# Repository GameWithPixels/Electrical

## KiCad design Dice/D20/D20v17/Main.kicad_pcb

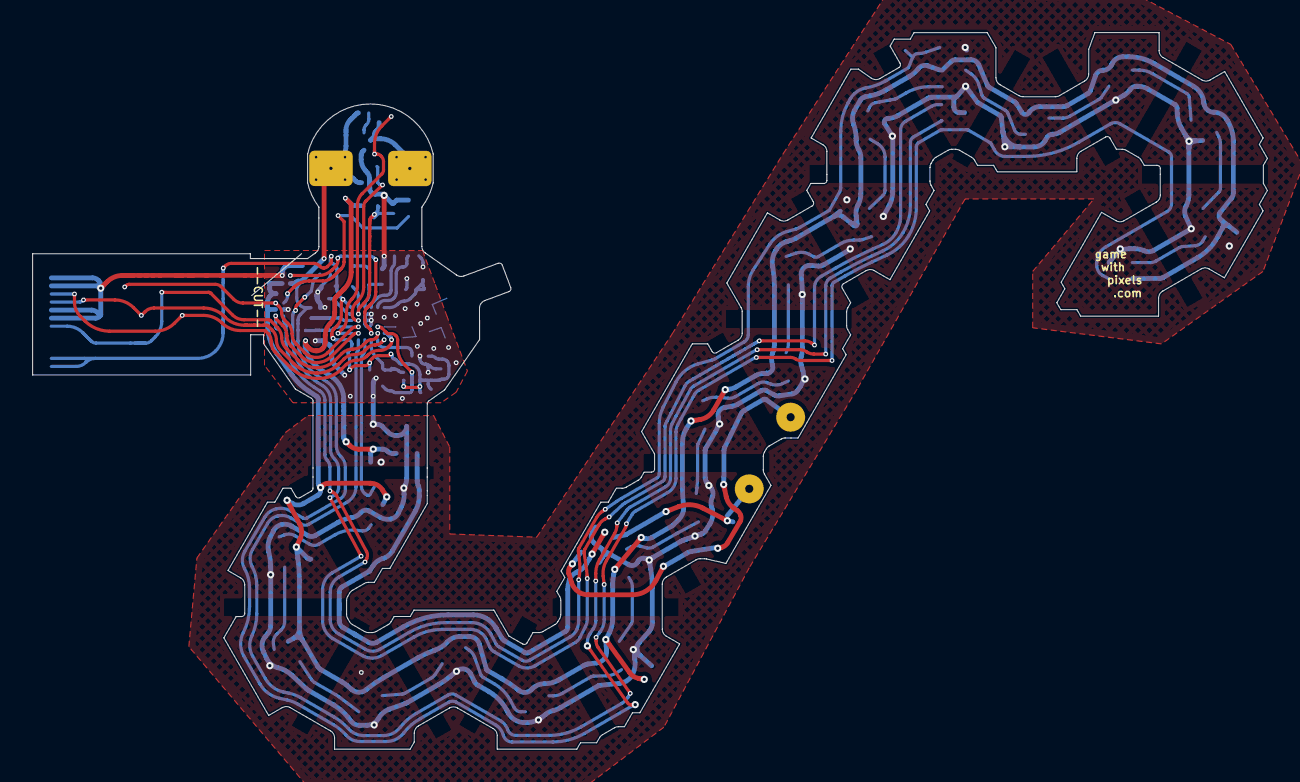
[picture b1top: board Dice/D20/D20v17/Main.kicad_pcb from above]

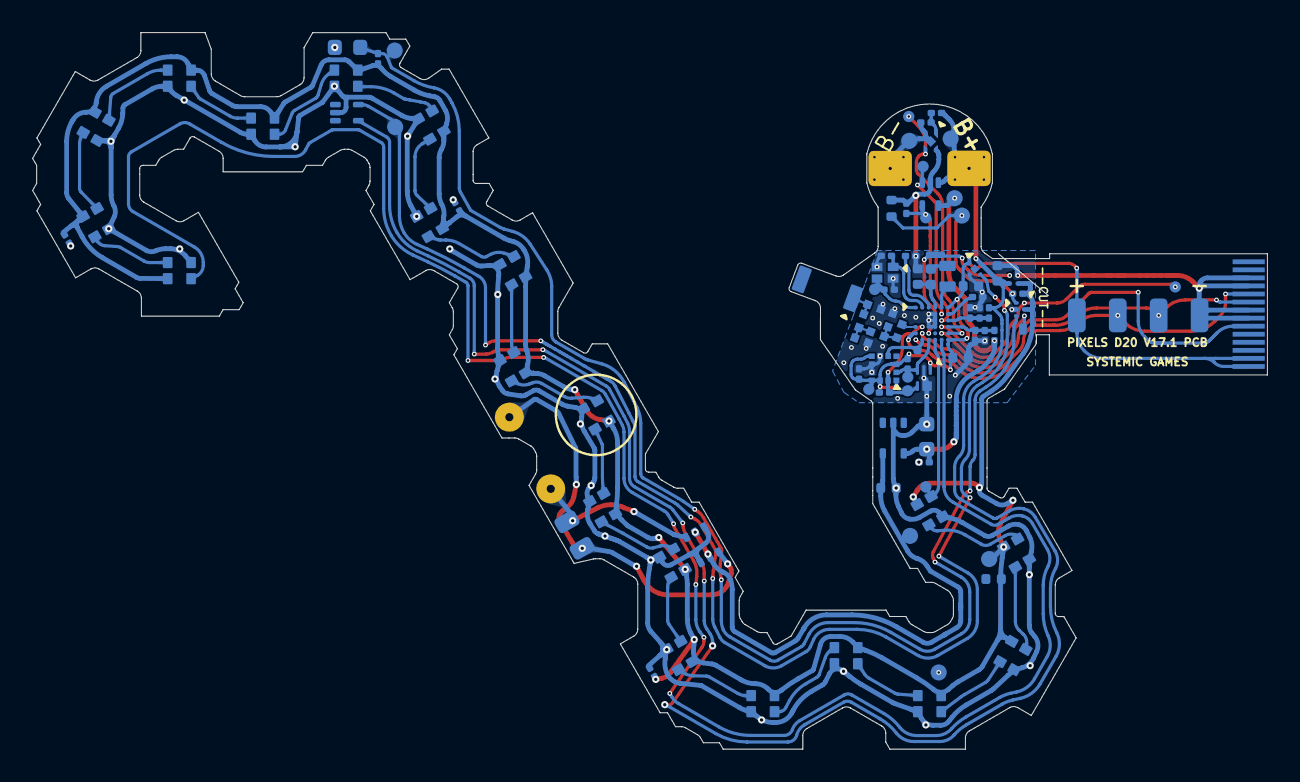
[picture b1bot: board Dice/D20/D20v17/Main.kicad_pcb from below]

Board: 2 copper layers, 76.7 x 44.5 mm, 99 parts (99 on the bottom side), 59 nets.

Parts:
AE1: Antenna_Chip; CHIP_ANT
C1, C4, C18: 4.7uF 10V 20%; C_0402_1005Metric
C2, C5: 8pF 10V 10%; C_0201_0603Metric
C3, C6, C10, C23, C24, C25: 0.1uF 10V 20%; C_0201_0603Metric
C7: 100pF NP0 10V 2%; C_0201_0603Metric
C8: 1.2pF 10V 5% C0G; 0402_RF
C9, C16: 10uF 6.3V 20%; C_0402_1005Metric
C11, C12: DNP; 0402_RF
C13: 4.7uF 25V 20%; C_0402_1005Metric
C15: 22uF 10V 20%; C_0603_1608Metric
C19: 12nF 50V 5% NP0; C_0805_2012Metric
C21, C22: 10nF 25V 10%; C_0201_0603Metric
D1: BAV99S; SOT-363_SC-70-6
D2, D3, D4, D5, D6, D7, D8, D9, D10, D11, D12, D13, D14, D15, D16, D17, D18, D19, D20, D21: TX1812MJA5; TX1812MWCA5-F01
J1: Conn_01x14; FPC_14
J2: Conn_01x04; FPC-POGO-4
J3: Conn_01x02; Hongjie 10100 Solder Tabs
L1: 10uH 100mA 20%; C_1.2x1.8
L2: 15nH 100mA 5%; L_0402_1005Metric
L3: 0 Ohm; 0402_RF
L4: 2.2nH 5%; 0402_RF
L5: 3.3nH 5%; 0402_RF
P5: COILA; TestPoint_THTPad_D1.5mm_Drill0.7mm_nosilk
P6: COILB; TestPoint_THTPad_D1.5mm_Drill0.7mm_nosilk
Q1: ZSPT-Z1608C-06F-Z4; D_0603_1608Metric
R1, R2, R7: 3.9M 1%; R_0201_0603Metric
R4, R5: 10k 1%; R_0201_0603Metric
R6, R10, R11: 3.9k 1%; R_0201_0603Metric
R8: 10M 1%; R_0201_0603Metric
R9: 100k 1%; R_0201_0603Metric
R12: 510R 1%; R_0201_0603Metric
TH1: NTC 100k @ 25C; R_0402_1005Metric
U1: NRF52810-CAAA-R; WLCSP
U2: KXTJ3-1057; LGA-12_2x2mm_P0.5mm
U3: TPS715; SOT-353_SC-70-5
U4: M24C02-FMH6TG; UFDFPN5
U5: AW35122
U6: ME6230; FPB1_1-4
U7: DS6101; UDFN-4-1EP_1x1mm_P0.65mm_EP0.48x0.48mm
U8: SL1605; SOT-553
U9: XT4051; SOT-553
U10: WAS3157D-6/TR; DFN1109-6
W1: LED_DATA1; TEST_PIN
W2: PROG; TEST_PIN
W3: PHOTO; TEST_PIN
W4: VDC; TEST_PIN
W5: SM; TEST_PIN
W6: MAG1; TEST_PIN
W7: ACC; TEST_PIN
W8: SCL; TEST_PIN
W9: SDA; TEST_PIN
W11: XC1; TEST_PIN
W14: BATT; TEST_PIN
W15: +5V; TEST_PIN
W16: VIN; TEST_PIN
W17: STAT; TEST_PIN
W19: GND; TEST_PIN
W20: TH1; TEST_PIN
W21: LED2; TEST_PIN
W22: ADC_S; TEST_PIN
W23: ADC_OUT; TEST_PIN
W24: B-; TEST_PIN
W25: VDD; TEST_PIN
Y1: 32MHz 40ppm; SX16Y032000B81T001

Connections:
+5V: C15.1, R1.1, R4.1, U3.5 (VOUT), U9.5 (VCC), W15.1
+BATT: C16.1, J3.1, R7.1, R12.1, U5.A2 (VIN), U6.4 (VIN), U8.4 (VDD), U9.1 (BAT), W14.1
/5V_SENSE: C21.1, R1.2, R2.2, U1.E6 (P0.05/AIN3)
/ACC_INT: U1.G2 (P0.20/TCLK), U2.5 (INT), W7.1
/ANTENNA: AE1.1 (FEED), C11.1, L3.2
/ANT_50: C12.1, L3.1, L5.2
/ANT_MID: C8.1, L4.2, L5.1
/ANT_NRF: L4.1, U1.E1 (ANT)
/LED_DATA: D2.3 (DIN), U1.G4 (P0.15), W1.1
/LED_EN: U1.F3 (P0.17), U5.B2 (EN), W21.1
/LED_RETURN: D21.1 (DOUT), U1.G5 (P0.12)
/MAG1_: U6.3 (CE), U8.5 (OUT), W6.1
/NTC_PHOTO_SENSE: U1.E5 (P0.04/AIN2), U10.6 (A), W23.1
/OPT_A2D: Q1.1 (C), R5.2, U10.3 (B1), W3.1
/PROG: R6.1, U1.B5 (P0.00/XL1), U9.4 (PROG), W2.1
/SCL: R10.2, U1.E2 (P0.18/TDATA0), U2.12 (SCL), U4.4 (SCL), W8.1
/SDA: R11.2, U1.G3 (P0.16/TDATA1), U2.2 (SDA), U4.3 (SDA), W9.1
/SENSE_SELECT: U1.F5 (P0.11), U10.4 (S), W22.1
/SM: U1.F6 (P0.8), U7.3 (SM), W5.1
/STATS: U1.D5 (P0.01/XL2), U9.3 (CHRG), W17.1
/VBAT_SENSE: C22.1, R7.2, R8.1, U1.D6 (P0.03/AIN1)
/Wireless Charging/B-: C23.2, J3.2, U7.2 (VSS), U7.5 (PAD), W24.1
/Wireless Charging/COILA: C19.1, D1.3 (K1A2), P5.1
/Wireless Charging/COILB: C19.2, D1.6 (K3A4), P6.1
/Wireless Charging/TH1: R9.2, TH1.1, U10.1 (B0), W20.1
GND: C1.2, C2.1, C3.2, C4.2, C5.1, C6.2, C7.2, C8.2, C9.2, C10.2, C11.2, C12.2, C13.2, C15.2, C16.2, C18.2, C21.2, C22.2, C24.2, C25.2, D1.1 (A1), D1.4 (A3), D2.2 (GND), D3.2 (GND), D4.2 (GND), D5.2 (GND), D6.2 (GND), D7.2 (GND), D8.2 (GND), D9.2 (GND), D10.2 (GND), D11.2 (GND), D12.2 (GND), D13.2 (GND), D14.2 (GND), D15.2 (GND), D16.2 (GND), D17.2 (GND), D18.2 (GND), D19.2 (GND), D20.2 (GND), D21.2 (GND), J1.3, J1.4, J1.7, J1.8, J2.4, Q1.2 (E), R2.1, R4.2, R6.2, R8.2, TH1.2, U1.B3 (VSS), U1.B4 (VSS), U1.C1 (VSS_PA), U1.D3 (VSS), U1.D4 (VSS), U1.E3 (VSS), U1.E4 (VSS), U2.6 (GND), U2.8 (GND), U2.9 (GND), U3.2 (GND), U4.2 (VSS), U4.5 (WP), U5.B1 (GND), U6.2 (VSS), U7.4 (EB-), U8.2 (GND), U9.2 (GND), U10.2 (GND), W19.1, Y1.2, Y1.4
unnamed: D2.1 (DOUT), D3.3 (DIN)
unnamed: D3.1 (DOUT), D4.3 (DIN)
unnamed: D4.1 (DOUT), D5.3 (DIN)
unnamed: D5.1 (DOUT), D6.3 (DIN)
unnamed: D6.1 (DOUT), D7.3 (DIN)
unnamed: D7.1 (DOUT), D8.3 (DIN)
unnamed: D8.1 (DOUT), D9.3 (DIN)
unnamed: D9.1 (DOUT), D10.3 (DIN)
unnamed: D10.1 (DOUT), D11.3 (DIN)
unnamed: D11.1 (DOUT), D12.3 (DIN)
unnamed: D12.1 (DOUT), D13.3 (DIN)
unnamed: D13.1 (DOUT), D14.3 (DIN)
unnamed: D14.1 (DOUT), D15.3 (DIN)
unnamed: D15.1 (DOUT), D16.3 (DIN)
unnamed: D16.1 (DOUT), D17.3 (DIN)
unnamed: D17.1 (DOUT), D18.3 (DIN)
unnamed: D18.1 (DOUT), D19.3 (DIN)
unnamed: D19.1 (DOUT), D20.3 (DIN)
unnamed: D20.1 (DOUT), D21.3 (DIN)
unnamed: L1.2, L2.1
unnamed: L1.1, U1.A5 (DCC)
unnamed: C3.1, U1.B6 (DEC1)
unnamed: C7.1, U1.A3 (DEC2)
unnamed: C1.1, L2.2, U1.A4 (DEC4)
unnamed: C5.2, U1.A1 (XC1), W11.1, Y1.3
unnamed: C2.2, U1.A2 (XC2), Y1.1
unnamed: C23.1, R12.2, U7.1 (BAT)
RESET: J1.9, U1.F2 (P0.21)
SWDCLK: J1.6, J2.3, U1.G1 (SWDCLK)
SWDIO: J1.5, J2.2, U1.F1 (SWDIO)
VDC: C6.1, C9.1, C24.1, C25.1, D2.4 (VCC), D3.4 (VCC), D4.4 (VCC), D5.4 (VCC), D6.4 (VCC), D7.4 (VCC), D8.4 (VCC), D9.4 (VCC), D10.4 (VCC), D11.4 (VCC), D12.4 (VCC), D13.4 (VCC), D14.4 (VCC), D15.4 (VCC), D16.4 (VCC), D17.4 (VCC), D18.4 (VCC), D19.4 (VCC), D20.4 (VCC), D21.4 (VCC), R5.1, R9.1, U5.A1 (VOUT), U10.5 (VCC), W4.1
VDD: C4.1, C10.1, C18.1, J1.13, J1.14, J2.1, R10.1, R11.1, U1.A6 (VDD), U1.G6 (VDD), U2.1 (ADDR), U2.3 (IO_VDD), U2.7 (VDD), U2.10 (VDD), U2.11 (IO_VDD), U4.1 (VCC), U6.1 (VOUT), W25.1
VEE: C13.1, D1.2 (K2), D1.5 (K4), U3.4 (VIN), W16.1

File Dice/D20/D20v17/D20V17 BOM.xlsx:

Reference | Value | Footprint | Qty | Manufacturer | Part Number | LCSC Part # |  | Alternate Manufacturer | Alternate PN | Alternate LCSC Part #
AE1 | Antenna_Chip | Pixels-dice:CHIP_ANT | 1 | Microgate | MGMA3216H2450-A02 | C486319
C1,C4,C18 | 4.7uF 10V 20% | Pixels-dice:C_0402_1005Metric | 3 | Murata | GRM155R61A475MEAAJ | C1849652 |  | Samsung Electro-Mechanics | CL05A475MP5NRNC | C23733
C2,C5 | 8pF 10V 10% | Capacitor_SMD:C_0201_0603Metric | 2 | FH (Guangdong Fenghua Advanced Tech) | 0201CG8R0C500NT | C501818 |  | Samsung Electro-Mechanics | CL10A475KA8NQNC
C3,C6,C10,C23,C24,C25 | 0.1uF 10V 20% | Capacitor_SMD:C_0201_0603Metric | 6 | HRE | CGA0201X5R104K100ET | C6119757
C7 | 100pF NP0 10V 2% | Capacitor_SMD:C_0201_0603Metric | 1 | HRE | CGA0201C0G101J500ET | C20069263 |  | EYANG(Shenzhen Eyang Tech Development) | C0201C0G101J500NTA | C115540
C8 | 1.2pF 10V 5% C0G | Pixels-dice:0402_RF | 1 | HRE | CGA0402C0G1R2C500GT | C20069293 |  | VIIYONG | V1R2B0402C0G500NBT | C513431
C9,C16 | 10uF 6.3V 20% | Pixels-dice:C_0402_1005Metric | 2 | HRE | CGA0402X5R106M6R3GT | C23692971
C13 | 4.7uF 25V 20% | Capacitor_SMD:C_0402_1005Metric | 1 | HRE | CGA0402X5R475M250GT | C6119795
C15 | 22uF 10V 20% | Capacitor_SMD:C_0603_1608Metric | 1 | HRE | CGA0603X5R226M100JT | C6119863
C19 | 12nF 50V 5% NP0 | Capacitor_SMD:C_0805_2012Metric | 1 | Murata | GRM2195C1H123JA01D | C97906
C21,C22 | 10nF 25V 10% | Capacitor_SMD:C_0201_0603Metric | 2 | HRE | CGA0201X5R103K250ET | C7503521 |  | Murata Electronics | GRM033R71A103KA01D | C76941
D1 | BAV99S | Pixels-dice:SOT-363_SC-70-6 | 1 | Nexperia | BAV99S,115 | C96225
D2,D3,D4,D5,D6,D7,D8,D9,D10,D11,D12,D13,D14,D15,D16,D17,D18,D19,D20,D21 | TX1812MJA5 | Pixels-dice:TX1812MWCA5-F01 | 20 | TCWIN | TX1812MJA5-F01
L1 | 10uH 100mA 20% | Pixels-dice:C_1.2x1.8 | 1 | Sunltech Tech | SLC1608F100KTT | C411908
L2 | 15nH 100mA 5% | Inductor_SMD:L_0402_1005Metric | 1 | FH | VHF100505H15NKT | C381880 |  | SUNLORD | MCL2012H100MT
L3 | 0 Ohm | Pixels-dice:0402_RF | 1 | UNI-ROYAL(Uniroyal Elec) | 0402WGJ0000TCE | C21376
L4 | 2.2nH 5% | Pixels-dice:0402_RF | 1 | FH | VHF100505HQ2N2ST | C395061
L5 | 3.3nH 5% | Pixels-dice:0402_RF | 1 | FH | VHF100505HQ3N3ST | C395065
Q1 | ZSPT-Z1608C-06F-Z4 | Diode_SMD:D_0603_1608Metric | 1 | Chau Light | ZSPT-Z1608C-06F-Z4 | C5337512
R1,R2,R7 | 3.9M 1% | Resistor_SMD:R_0201_0603Metric | 3 | UNI-ROYAL(Uniroyal Elec) | 0201WMF3904TEE | C423545 |  | RALEC | RTT013904FTH | C166210
R4,R5 | 10k 1% | Resistor_SMD:R_0201_0603Metric | 2 | UNI-ROYAL(Uniroyal Elec) | 0201WMF1002TEE | C473048
R6,R10,R11 | 3.9k 1% | Resistor_SMD:R_0201_0603Metric | 3 | UNI-ROYAL(Uniroyal Elec) | 0201WMF3651TEE | C516477 |  | UNI-ROYAL(Uniroyal Elec)
R8 | 10M 1% | Resistor_SMD:R_0201_0603Metric | 1 | UNI-ROYAL(Uniroyal Elec) | 0201WMF1005TEE | C423797
R9 | 100k 1% | Resistor_SMD:R_0201_0603Metric | 1 | UNI-ROYAL(Uniroyal Elec) | 0201WMF1003TEE | C270364
R12 | 510R 1% | Resistor_SMD:R_0201_0603Metric | 1 | UNI-ROYAL(Uniroyal Elec) | NQ01WMJ0511TEE | C965307
TH1 | NTC 100k @ 25C | Pixels-dice:R_0402_1005Metric | 1 | TDK | NTCG104EF104FT1X | C107344
U1 | NRF52810-CAAA-R | Pixels-dice:WLCSP | 1 | Nordic | NRF52810-CAAA-R | C3606661
U2 | KXTJ3-1057 | Package_LGA:LGA-12_2x2mm_P0.5mm | 1 | Kionix | KXTJ3-1057 | C442603
U3 | TPS715 | Package_TO_SOT_SMD:SOT-353_SC-70-5 | 1 | TECH PUBLIC | TPS71550DCKR-TP | C7202975 |  | Texas Instruments | TPS71550DCKR | C571193
U4 | M24C02-FMH6TG | Pixels-dice:UFDFPN5 | 1 | STMicroelectronics | M24C02-FMH6TG | C222197
U5 | AW35122 | Pixels-dice:AW35122 | 1 | AWINIC(Shanghai Awinic Tech) | AW35122FDR | C5125911
U6 | ME6230 | Pixels-dice:FPB1_1-4 | 1 | MICRONE(Nanjing Micro One Elec) | ME6230C30U4AG | C2925772 |  | ChipLink Tech | CL9906A30F4N | C5297658
U7 | DS6101 | Package_DFN_QFN:UDFN-4-1EP_1x1mm_P0.65mm_EP0.48x0.48mm | 1 | DSTECH | DS6101AED4 | C7499469
U8 | SL1605 | Package_TO_SOT_SMD:SOT-553 | 1 | Slkor(SLKORMICRO Elec.) | SL1605TL | C2826474
U9 | XT4051 | Package_TO_SOT_SMD:SOT-553 | 1 | NATLINEAR | XT4051K421KR-G | C219186
U10 | WAS3157D-6/TR | Pixels-dice:DFN1109-6 | 1 | WILLSEMI(Will Semicon) | WAS3157D-6/TR | C2939860
Y1 | 32MHz 40ppm | Pixels-dice:SX16Y032000B81T001 | 1 | TKD | SX16Y032000B81T001 | C20623629 |  | TXC Corp | 8Q32000002 | C5203640

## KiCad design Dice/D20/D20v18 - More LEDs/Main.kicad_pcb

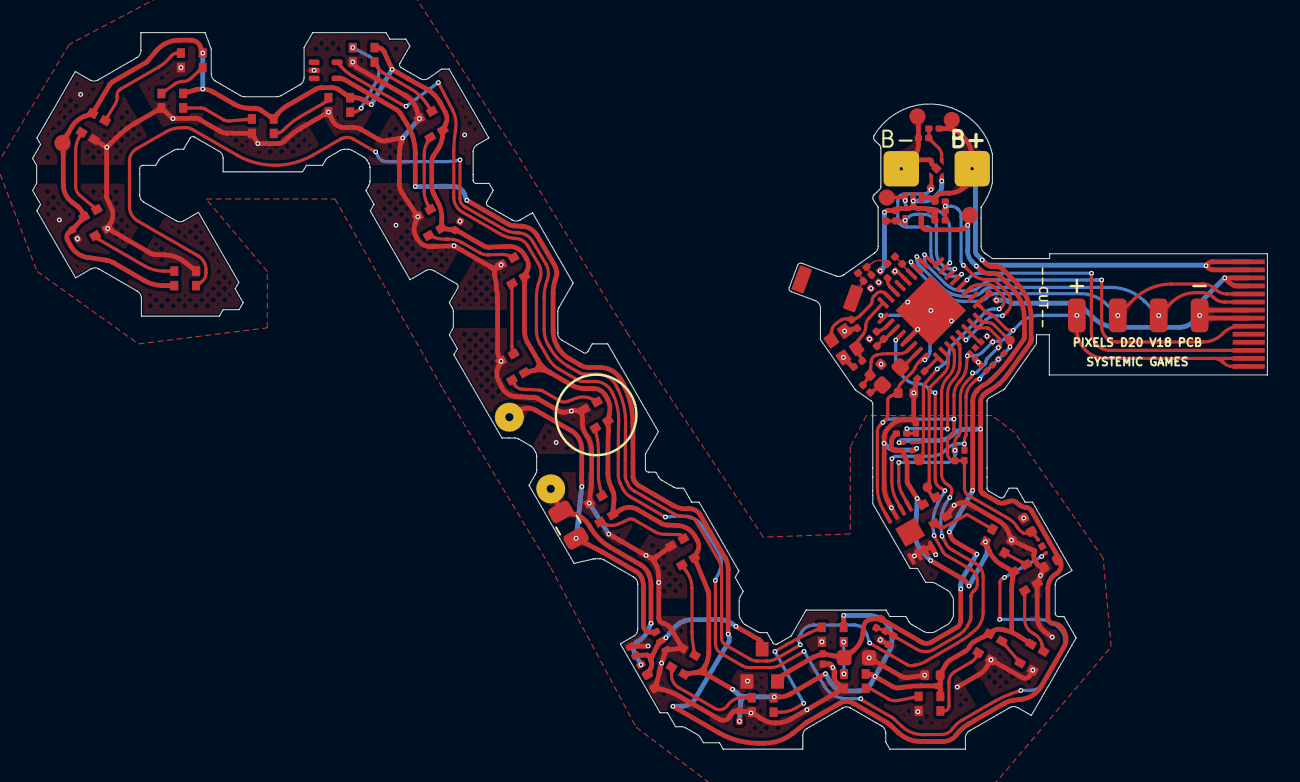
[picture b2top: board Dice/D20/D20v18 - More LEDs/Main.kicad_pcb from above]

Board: 2 copper layers, 76.7 x 44.5 mm, 92 parts (1 on the bottom side), 63 nets.

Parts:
AE1: Antenna_Chip; CHIP_ANT
C1, C4, C18: 4.7uF 10V 20%; C_0402_1005Metric
C2, C5: 8pF 10V 10%; C_0201_0603Metric
C3, C6, C10, C23, C24, C25: 0.1uF 10V 20%; C_0201_0603Metric
C7: 100pF NP0 10V 2%; C_0201_0603Metric
C8: 0.8pF 10V 5% C0G; C_0201_0603Metric
C9, C16: 10uF 6.3V 20%; C_0402_1005Metric
C11, C12: DNP; C_0201_0603Metric
C13: 4.7uF 25V 20%; C_0402_1005Metric
C15: 22uF 10V 20%; C_0603_1608Metric
C19: 12nF 50V 5% NP0; C_0805_2012Metric
C21, C22: 10nF 25V 10%; C_0201_0603Metric
D1: BAV99S; SOT-363_SC-70-6
D2, D3, D4, D5, D6, D7, D8, D9, D10, D11, D12, D13, D14, D15, D16, D17, D18, D19, D20, D21, D22, D23, D24, D29, D30: TX1812MJA5; TX1812MWCA5-F01
J1: Conn_01x14; FPC_14
J2: Conn_01x04; FPC-POGO-4
J3: Conn_01x02; Hongjie 10100 Solder Tabs
L1: 10uH 100mA 20%; L_0603_1608Metric
L2: 15nH 100mA 5%; L_0201_0603Metric
L3: 1.8nH 5%; L_0201_0603Metric
L5: 3.9nH 5%; L_0201_0603Metric
P5: COILA; TestPoint_THTPad_D1.5mm_Drill0.7mm_nosilk
P6: COILB; TestPoint_THTPad_D1.5mm_Drill0.7mm_nosilk
R1, R2, R7: 3.9M 1%; R_0201_0603Metric
R3: 348k 1%; R_0201_0603Metric
R4: 10k 1%; R_0201_0603Metric
R5, R9: 100k 1%; R_0201_0603Metric
R6: 3.57k 1%; R_0201_0603Metric
R8: 10M 1%; R_0201_0603Metric
R10, R11: 3.9k 1%; R_0201_0603Metric
R12: 510R 1%; R_0201_0603Metric
TH1: NTC 100k @ 25C; R_0201_0603Metric
U1: N52810_QFN32; QFN-32-1EP_5x5mm_P0.5mm_EP3.1x3.1mm
U2: SC7A20HTR; LGA-12_2x2mm_P0.5mm
U3: PJ75BL50SA; SOT-23
U4: BL24C02F-NTRC; TDFN-8-1EP_3x2mm_P0.5mm_EP1.3x1.4mm
U5: AW35122
U6: ME6230; FPB1_1-4
U7: DS6101; UDFN-4-1EP_1x1mm_P0.65mm_EP0.48x0.48mm
U8: SL1605; SOT-553
U9: XT4051; SOT-553
W1: LED_DATA1; TEST_PIN
W2: PROG; TEST_PIN
W4: VDC; TEST_PIN
W5: SM; TEST_PIN
W8: SCL; TEST_PIN
W9: SDA; TEST_PIN
W14: BATT; TEST_PIN
W15: +5V; TEST_PIN
W17: STAT; TEST_PIN
W21: LED2; TEST_PIN
W24: B-; TEST_PIN
Y1: 32MHz 40ppm; Crystal_SMD_2016-4Pin_2.0x1.6mm

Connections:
+5V: C15.1, R1.1, R4.1, U3.2 (VOUT), U9.5 (VCC), W15.1
+BATT: C16.1, J1.1, J1.2, J3.1, R7.1, R12.1, U5.A2 (VIN), U6.4 (VIN), U8.4 (VDD), U9.1 (BAT), W14.1
/ACC_INT: U1.6 (P0.06), U2.5 (INT1)
/ANTENNA: AE1.1 (FEED), C11.1, L3.2
/ANT_50: C12.1, L3.1, L5.2
/ANT_NRF: C8.1, L5.1, U1.19 (ANT)
/LEDs/LED_DATA: D2.3 (DIN), U1.2 (P0.00/XL1), W1.1
/LEDs/LED_RETURN: D21.1 (DOUT), U1.3 (P0.01/XL2)
/SCL: R10.2, U1.8 (P0.10), U2.12 (SCL), U4.6 (SCL), W8.1
/SDA: R11.2, U1.7 (P0.09), U2.2 (SDA), U4.5 (SDA), W9.1
/Wireless Charging/B-: C23.2, J3.2, U7.2 (VSS), U7.5 (PAD), W24.1
/Wireless Charging/COILA: C19.1, D1.3 (K1A2), P5.1
/Wireless Charging/COILB: C19.2, D1.6 (K3A4), P6.1
/Wireless Charging/COIL_SENSE: C21.1, R1.2, R2.2, U1.28 (P0.30/AIN6)
/Wireless Charging/LED_EN_OUT: U1.11 (P0.14), U5.B2 (EN), W21.1
/Wireless Charging/MAG1_: U6.3 (CE), U8.5 (OUT)
/Wireless Charging/PROG: R6.1, U1.14 (P0.18/TDATA0), U9.4 (PROG), W2.1
/Wireless Charging/SM: U1.13 (P0.16/TDATA1), U7.3 (SM), W5.1
/Wireless Charging/STAT: U1.15 (P0.20/TCLK), U9.3 (CHRG), W17.1
/Wireless Charging/TH1: R9.2, TH1.1, U1.4 (P0.04/AIN2)
/Wireless Charging/VBAT_SENSE: C22.1, R7.2, R8.1, U1.5 (P0.05/AIN3)
GND: C1.2, C2.1, C3.2, C4.2, C5.1, C6.2, C7.2, C8.2, C9.2, C10.2, C11.2, C12.2, C13.2, C15.2, C16.2, C18.2, C21.2, C22.2, C24.2, C25.2, D1.1 (A1), D1.4 (A3), D2.2 (GND), D3.2 (GND), D4.2 (GND), D5.2 (GND), D6.2 (GND), D7.2 (GND), D8.2 (GND), D9.2 (GND), D10.2 (GND), D11.2 (GND), D12.2 (GND), D13.2 (GND), D14.2 (GND), D15.2 (GND), D16.2 (GND), D17.2 (GND), D18.2 (GND), D19.2 (GND), D20.2 (GND), D21.2 (GND), D22.2 (GND), D23.2 (GND), D24.2 (GND), D29.2 (GND), D30.2 (GND), J1.3, J1.4, J1.7, J1.8, J2.4, R2.1, R3.1, R4.2, R6.2, R8.2, TH1.2, U1.20 (VSS), U1.29 (VSS), U1.33 (VSS), U2.4 (NC), U2.8 (GND), U2.9 (GND), U3.1 (VSS), U4.1 (A0), U4.2 (A1), U4.3 (A2), U4.4 (GND), U4.7 (WP), U5.B1 (GND), U6.2 (VSS), U7.4 (EB-), U8.2 (GND), U9.2 (GND), Y1.2, Y1.4
unnamed: D2.1 (DOUT), D3.3 (DIN)
unnamed: D5.1 (DOUT), D6.3 (DIN)
unnamed: D7.1 (DOUT), D8.3 (DIN)
unnamed: D8.1 (DOUT), D9.3 (DIN)
unnamed: D9.1 (DOUT), D10.3 (DIN)
unnamed: D10.1 (DOUT), D11.3 (DIN)
unnamed: D11.1 (DOUT), D12.3 (DIN)
unnamed: D12.1 (DOUT), D13.3 (DIN)
unnamed: D13.1 (DOUT), D14.3 (DIN)
unnamed: D14.1 (DOUT), D15.3 (DIN)
unnamed: D15.1 (DOUT), D16.3 (DIN)
unnamed: D16.1 (DOUT), D29.3 (DIN)
unnamed: D17.3 (DIN), D29.1 (DOUT)
unnamed: D17.1 (DOUT), D18.3 (DIN)
unnamed: D18.1 (DOUT), D30.3 (DIN)
unnamed: D19.3 (DIN), D30.1 (DOUT)
unnamed: D19.1 (DOUT), D20.3 (DIN)
unnamed: D20.1 (DOUT), D21.3 (DIN)
unnamed: D3.1 (DOUT), D22.3 (DIN)
unnamed: D4.3 (DIN), D22.1 (DOUT)
unnamed: D4.1 (DOUT), D23.3 (DIN)
unnamed: D5.3 (DIN), D23.1 (DOUT)
unnamed: D6.1 (DOUT), D24.3 (DIN)
unnamed: D7.3 (DIN), D24.1 (DOUT)
unnamed: L1.2, L2.1
unnamed: L1.1, U1.31 (DCC)
unnamed: C3.1, U1.1 (DEC1)
unnamed: C7.1, U1.22 (DEC3)
unnamed: C1.1, L2.2, U1.30 (DEC4)
unnamed: R5.2, U1.26 (P0.25)
unnamed: R3.2, R5.1, U1.27 (P0.28/AIN4)
unnamed: C5.2, U1.23 (XC1), Y1.3
unnamed: C2.2, U1.24 (XC2), Y1.1
unnamed: C23.1, R12.2, U7.1 (BAT)
RESET: J1.9, U1.16 (P0.16)
SWDCLK: J1.6, J2.3, U1.17 (SWDCLK)
SWDIO: J1.5, J2.2, U1.18 (SWDIO)
TX: J1.12, U1.12 (P0.15)
VDC: C6.1, C9.1, C24.1, C25.1, D2.4 (VCC), D3.4 (VCC), D4.4 (VCC), D5.4 (VCC), D6.4 (VCC), D7.4 (VCC), D8.4 (VCC), D9.4 (VCC), D10.4 (VCC), D11.4 (VCC), D12.4 (VCC), D13.4 (VCC), D14.4 (VCC), D15.4 (VCC), D16.4 (VCC), D17.4 (VCC), D18.4 (VCC), D19.4 (VCC), D20.4 (VCC), D21.4 (VCC), D22.4 (VCC), D23.4 (VCC), D24.4 (VCC), D29.4 (VCC), D30.4 (VCC), R9.1, U5.A1 (VOUT), W4.1
VDD: C4.1, C10.1, C18.1, J1.13, J1.14, J2.1, R10.1, R11.1, U1.9 (VDD), U1.25 (VDD), U1.32 (VDD), U2.3 (IO_VDD), U2.7 (VDD), U4.8 (VCC), U6.1 (VOUT)
VEE: C13.1, D1.2 (K2), D1.5 (K4), U3.3 (VIN)

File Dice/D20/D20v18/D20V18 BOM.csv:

"Reference","Qty","Value","DNP","Footprint","Manufacturer","Part Number"
"AE1","1","Antenna_Chip","","Pixels-dice:CHIP_ANT","Microgate","MGMA3216H2450-A02"
"C1,C4,C18","3","4.7uF 10V 20%","","Pixels-dice:C_0402_1005Metric","HRE","CGA0402X5R475M100GT"
"C2,C5","2","8pF 10V 10%","","Capacitor_SMD:C_0201_0603Metric","HRE","CGA0201C0G8R0B250ET"
"C3,C6,C10,C23,C24,C25","6","0.1uF 10V 20%","","Capacitor_SMD:C_0201_0603Metric","HRE","CGA0201X5R104K100ET"
"C7","1","100pF NP0 10V 2%","","Capacitor_SMD:C_0201_0603Metric","HRE","CGA0201C0G101J500ET"
"C8","1","0.8pF 10V 5% C0G","","Capacitor_SMD:C_0201_0603Metric","HRE","CGA0201C0GR80C250ET"
"C9,C16","2","10uF 6.3V 20%","","Pixels-dice:C_0402_1005Metric","HRE","CGA0402X5R106M6R3GT"
"C13","1","4.7uF 25V 20%","","Capacitor_SMD:C_0402_1005Metric","HRE","CGA0402X5R475M250GT"
"C15","1","22uF 10V 20%","","Capacitor_SMD:C_0603_1608Metric","HRE","CGA0603X5R226M100JT"
"C19","1","12nF 50V 5% NP0","","Capacitor_SMD:C_0805_2012Metric","Murata","GRM2195C1H123JA01D"
"C21,C22","2","10nF 25V 10%","","Capacitor_SMD:C_0201_0603Metric","HRE","CGA0201X5R103K250ET"
"D1","1","BAV99S","","Pixels-dice:SOT-363_SC-70-6","Nexperia","BAV99S,115"
"D2,D3,D4,D5,D6,D7,D8,D9,D10,D11,D12,D13,D14,D15,D16,D17,D18,D19,D20,D21","20","TX1812MJA5","","Pixels-dice:TX1812MWCA5-F01","TCWIN","TX1812MJA5-F01"
"L1","1","10uH 100mA 20%","","Inductor_SMD:L_0603_1608Metric","FH","CMI160808J100KT"
"L2","1","15nH 100mA 5%","","Inductor_SMD:L_0201_0603Metric","FH","VHF060303HQ15NKT"
"L3","1","1.8nH 5%","","Inductor_SMD:L_0201_0603Metric","FH","VHF060303HQ1N8ST"
"L5","1","3.9nH 5%","","Inductor_SMD:L_0201_0603Metric","FH"," VHF060303HQ3N9ST02"
"R1,R2,R7","3","3.9M 1%","","Resistor_SMD:R_0201_0603Metric","UNI-ROYAL(Uniroyal Elec)","0201WMF3904TEE"
"R3","1","348k 1%","","Resistor_SMD:R_0201_0603Metric","UNI-ROYAL(Uniroyal Elec)","0201WMF3483TEE"
"R4","1","10k 1%","","Resistor_SMD:R_0201_0603Metric","UNI-ROYAL(Uniroyal Elec)","0201WMF1002TEE"
"R5,R9","2","100k 1%","","Resistor_SMD:R_0201_0603Metric","UNI-ROYAL(Uniroyal Elec)","0201WMF1003TEE"
"R6","1","3.57k 1%","","Resistor_SMD:R_0201_0603Metric","UNI-ROYAL(Uniroyal Elec)","0201WMF3571TEE"
"R8","1","10M 1%","","Resistor_SMD:R_0201_0603Metric","UNI-ROYAL(Uniroyal Elec)","0201WMF1005TEE"
"R10,R11","2","3.9k 1%","","Resistor_SMD:R_0201_0603Metric","UNI-ROYAL(Uniroyal Elec)","0201WMF3651TEE"
"R12","1","510R 1%","","Resistor_SMD:R_0201_0603Metric","UNI-ROYAL(Uniroyal Elec)","NQ01WMJ0511TEE"
"TH1","1","NTC 100k @ 25C","","Resistor_SMD:R_0201_0603Metric","muRata ","NCP03WF104F05RL "
"U1","1","N52810_QFN32","","Pixels-dice:QFN-32-1EP_5x5mm_P0.5mm_EP3.1x3.1mm","Nordic Semiconductor","NRF52810-QCAA-R"
"U2","1","SC7A20HTR","","Package_LGA:LGA-12_2x2mm_P0.5mm","Hangzhou Silan Microelectronics","SC7A20HTR"
"U3","1","PJ75BL50SA","","Pixels-dice:SOT-23","PJSEMI","PJ75BL50SA"
"U4","1","BL24C02F-NTRC","","Pixels-dice:TDFN-8-1EP_3x2mm_P0.5mm_EP1.3x1.4mm","BL","BL24C02F-NTRC"
"U5","1","AW35122","","Pixels-dice:AW35122","AWINIC(Shanghai Awinic Tech)","AW35122FDR"
"U6","1","ME6230","","Pixels-dice:FPB1_1-4","MICRONE(Nanjing Micro One Elec)","ME6230C30U4AG"
"U7","1","DS6101","","Package_DFN_QFN:UDFN-4-1EP_1x1mm_P0.65mm_EP0.48x0.48mm","DSTECH"," DS6101AED4"
"U8","1","SL1605","","Package_TO_SOT_SMD:SOT-553","Slkor(SLKORMICRO Elec.)","SL1605TL"
"U9","1","XT4051","","Package_TO_SOT_SMD:SOT-553","NATLINEAR","XT4051K421KR-G"
"Y1","1","32MHz 40ppm","","Pixels-dice:Crystal_SMD_2016-4Pin_2.0x1.6mm","TOGNJING","XTM20032000DT00351001"

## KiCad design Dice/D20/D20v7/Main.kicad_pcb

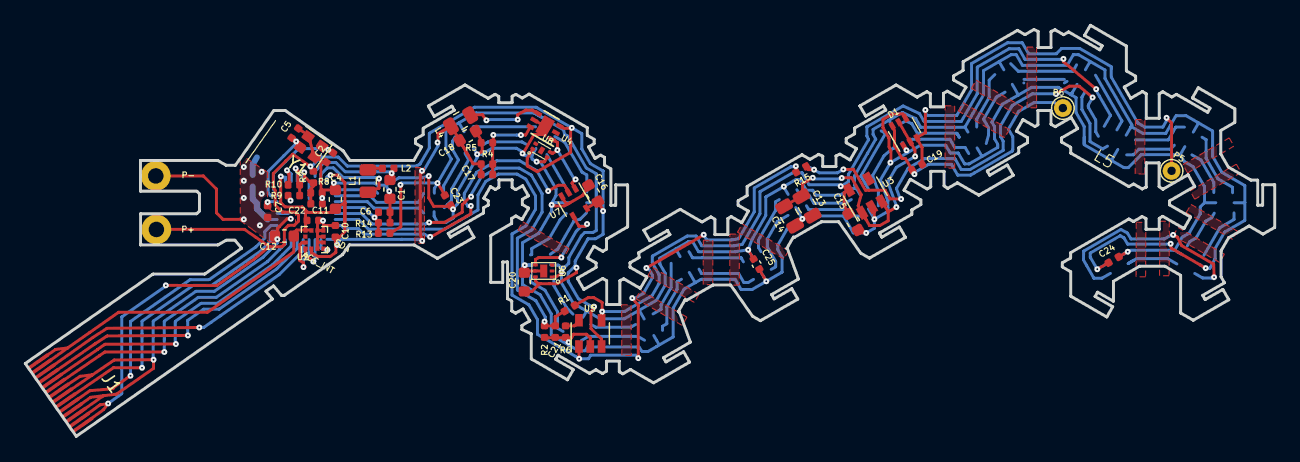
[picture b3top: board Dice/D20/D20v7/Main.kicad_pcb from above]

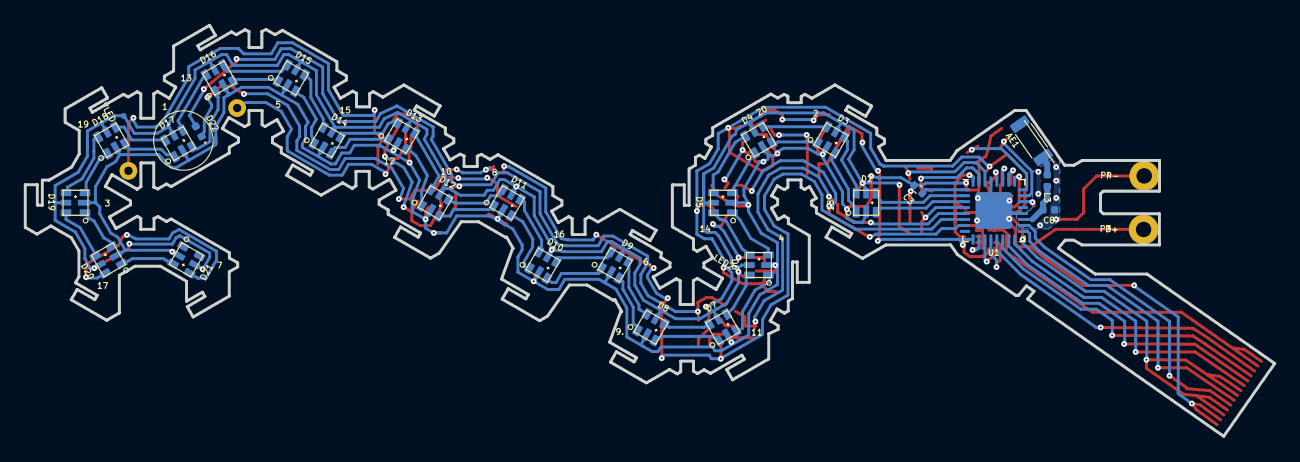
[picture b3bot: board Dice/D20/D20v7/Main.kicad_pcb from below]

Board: 2 copper layers, 105.1 x 34.6 mm, 81 parts (30 on the bottom side), 79 nets.

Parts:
AE1: Antenna; CHIP_ANT
C1, C4, C12, C15, C16, C18, C20: 4.7uF 6.3V 20%; C_0603_1608Metric
C2, C5: 6pF 10V 10%; C_0402_1005Metric
C3, C10, C11, C23, C24, C25: 0.1uF 10V 20%; C_0402_1005Metric
C6, C21, C22: 10nF 25V 10%; C_0402_1005Metric
C7: 100pF NP0 10V 5%; C_0402_1005Metric
C8: 0.8pF NP0 10V 5%; C_0402_1005Metric
C13, C14: 10uF 25V 20%; C_0805_2012Metric
C17: 22pF 10V 5%; C_0402_1005Metric
C19: 500pF 50V 10%; C_0402_1005Metric
D1: BAV99S; SOT-363_SC-70-6
D2, D3, D4, D5, D6, D7, D8, D9, D10, D11, D12, D13, D14, D15, D16, D17, D18, D19, D20, D21: APA102; APA102-2020-256-6
D22: LED; LED_0402_1005Metric
J1: Conn_01x14; FPC_14
L1: 10uH 100mA 10%; L_0805_2012Metric
L2: 15nH 100mA 5%; L_0402_1005Metric
L3: 3.9nH 100 mA 5%; L_0402_1005Metric
L4: 2.2uH 20mA 10%; L_0805_2012Metric
P3: BATT+; BatteryConnector
P4: BATT-; BatteryConnector
P5: COILA; TestPoint_THTPad_D1.5mm_Drill0.7mm
P6: COILB; TestPoint_THTPad_D1.5mm_Drill0.7mm
R1, R7, R13: 4M 1%; R_0402_1005Metric
R2, R8, R14: 10M 1%; R_0402_1005Metric
R4: 402k 1%; R_0402_1005Metric
R5, R10: 100k 1%; R_0402_1005Metric
R6: 10k 5%; R_0402_1005Metric
R9: 68K 1%; R_0402_1005Metric
R15: 200 5%; R_0402_1005Metric
U1: N52810_QFN32; QFN-32-1EP_5x5mm_P0.5mm_EP3.1x3.1mm
U2: LIS2DE12; LGA-12_2x2mm_P0.5mm
U3: AP2204K-5.0; SOT-23-5
U4: AP3401; DFN-6-1EP_2x2mm_P0.65mm_EP1x1.6mm
U5: MCP73832T-2ACI/OT; SOT-23-5
U6: MIC2095-1; MLF_1.6x1.6_6
U7: 74AHC1G08; SOT-353_SC-70-5
U8: BU52272NUZ; VSON04Z1114A
W3: VLED; TEST_PIN
W7: ACC_INT; TEST_PIN
W9: SDA; TEST_PIN
W21: LED2; TEST_PIN
Y1: 32MHz 40ppm; Crystal_SMD_2016-4Pin_2.0x1.6mm

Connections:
+5V: C15.1, D22.2, R1.1, U3.5, U5.4
/5V_SENSE: C21.1, R1.2, R2.2, U1.5
/ACC_INT: U1.12, U2.12, W7.1
/ANTENNA: AE1.1, L3.2
/ANT_CHIP: C8.1, L3.1, U1.19
/LED_CLK: D2.4, U1.2
/LED_DATA: D2.3, U1.3
/LED_EN: U1.7, U7.2
/Power/LED_EN_OUT: U6.4, U7.4, W21.1
/Power/MAG1_: U4.1, U7.1, U8.3
/SCL: U1.11, U2.1
/SDA: U1.10, U2.4, W9.1
/STATS: R15.2, U1.6, U5.1
/VBAT_SENSE: C22.1, R7.2, R8.1, U1.28
/VLED_SENSE: C6.1, R13.2, R14.1, U1.4
GND: C1.2, C2.1, C3.2, C4.2, C5.1, C6.2, C7.2, C8.2, C10.2, C11.1, C12.1, C13.2, C14.2, C15.2, C16.2, C18.2, C20.2, C21.2, C22.2, C23.2, C24.2, C25.2, D1.1, D1.4, D2.2, D3.2, D4.2, D5.2, D6.2, D7.2, D8.2, D9.2, D10.2, D11.2, D12.2, D13.2, D14.2, D15.2, D16.2, D17.2, D18.2, D19.2, D20.2, D21.2, J1.3, J1.4, J1.7, J1.8, P4.1, R2.1, R5.1, R6.2, R8.2, R9.1, R14.2, U1.20, U1.29, U1.33, U2.3, U2.5, U2.6, U2.7, U2.8, U3.2, U4.5, U4.7, U5.2, U6.5, U6.7, U7.3, U8.2, Y1.2, Y1.4
unnamed: C1.1, L2.2, U1.30
unnamed: C2.2, U1.24, Y1.1
unnamed: C3.1, U1.1
unnamed: C5.2, U1.23, Y1.3
unnamed: C7.1, U1.22
unnamed: C13.1, C14.1, D1.2, D1.5, U3.1, U3.3
unnamed: C17.2, R4.1, R5.2, U4.6
unnamed: C19.1, D1.3, P5.1
unnamed: C19.2, D1.6, P6.1
unnamed: D2.1, D3.3
unnamed: D2.6, D3.4
unnamed: D3.1, D4.3
unnamed: D3.6, D4.4
unnamed: D4.1, D5.3
unnamed: D4.6, D5.4
unnamed: D5.1, D6.3
unnamed: D5.6, D6.4
unnamed: D6.1, D7.3
unnamed: D6.6, D7.4
unnamed: D7.1, D8.3
unnamed: D7.6, D8.4
unnamed: D8.1, D9.3
unnamed: D8.6, D9.4
unnamed: D10.1, D11.3
unnamed: D9.1, D10.3
unnamed: D9.6, D10.4
unnamed: D10.6, D11.4
unnamed: D11.1, D12.3
unnamed: D11.6, D12.4
unnamed: D12.1, D13.3
unnamed: D12.6, D13.4
unnamed: D13.1, D14.3
unnamed: D13.6, D14.4
unnamed: D14.1, D15.3
unnamed: D14.6, D15.4
unnamed: D15.1, D16.3
unnamed: D15.6, D16.4
unnamed: D16.1, D17.3
unnamed: D16.6, D17.4
unnamed: D17.1, D18.3
unnamed: D17.6, D18.4
unnamed: D18.1, D19.3
unnamed: D18.6, D19.4
unnamed: D19.1, D20.3
unnamed: D19.6, D20.4
unnamed: D20.1, D21.3
unnamed: D20.6, D21.4
unnamed: D22.1, R15.1
unnamed: L1.1, U1.31
unnamed: L1.2, L2.1
unnamed: L4.1, U4.4
unnamed: R6.1, U5.5
unnamed: R9.2, R10.1, U1.27
unnamed: R10.2, U1.26
RESET: J1.9, U1.16
RXI: J1.10, U1.15
SWDCLK: J1.6, U1.17
SWDIO: J1.5, U1.18
SWO: J1.11, U1.14
TXO: J1.12, U1.13
VBAT: C16.1, C20.1, J1.1, J1.2, P3.1, R7.1, U4.3, U5.3, U6.6, U7.5, U8.1
VDD: C4.1, C10.1, C11.2, C12.2, C17.1, C18.1, J1.13, J1.14, L4.2, R4.2, U1.9, U1.25, U1.32, U2.2, U2.9, U2.10
VLED: C23.1, C24.1, C25.1, D2.5, D3.5, D4.5, D5.5, D6.5, D7.5, D8.5, D9.5, D10.5, D11.5, D12.5, D13.5, D14.5, D15.5, D16.5, D17.5, D18.5, D19.5, D20.5, D21.5, R13.1, U6.1, W3.1

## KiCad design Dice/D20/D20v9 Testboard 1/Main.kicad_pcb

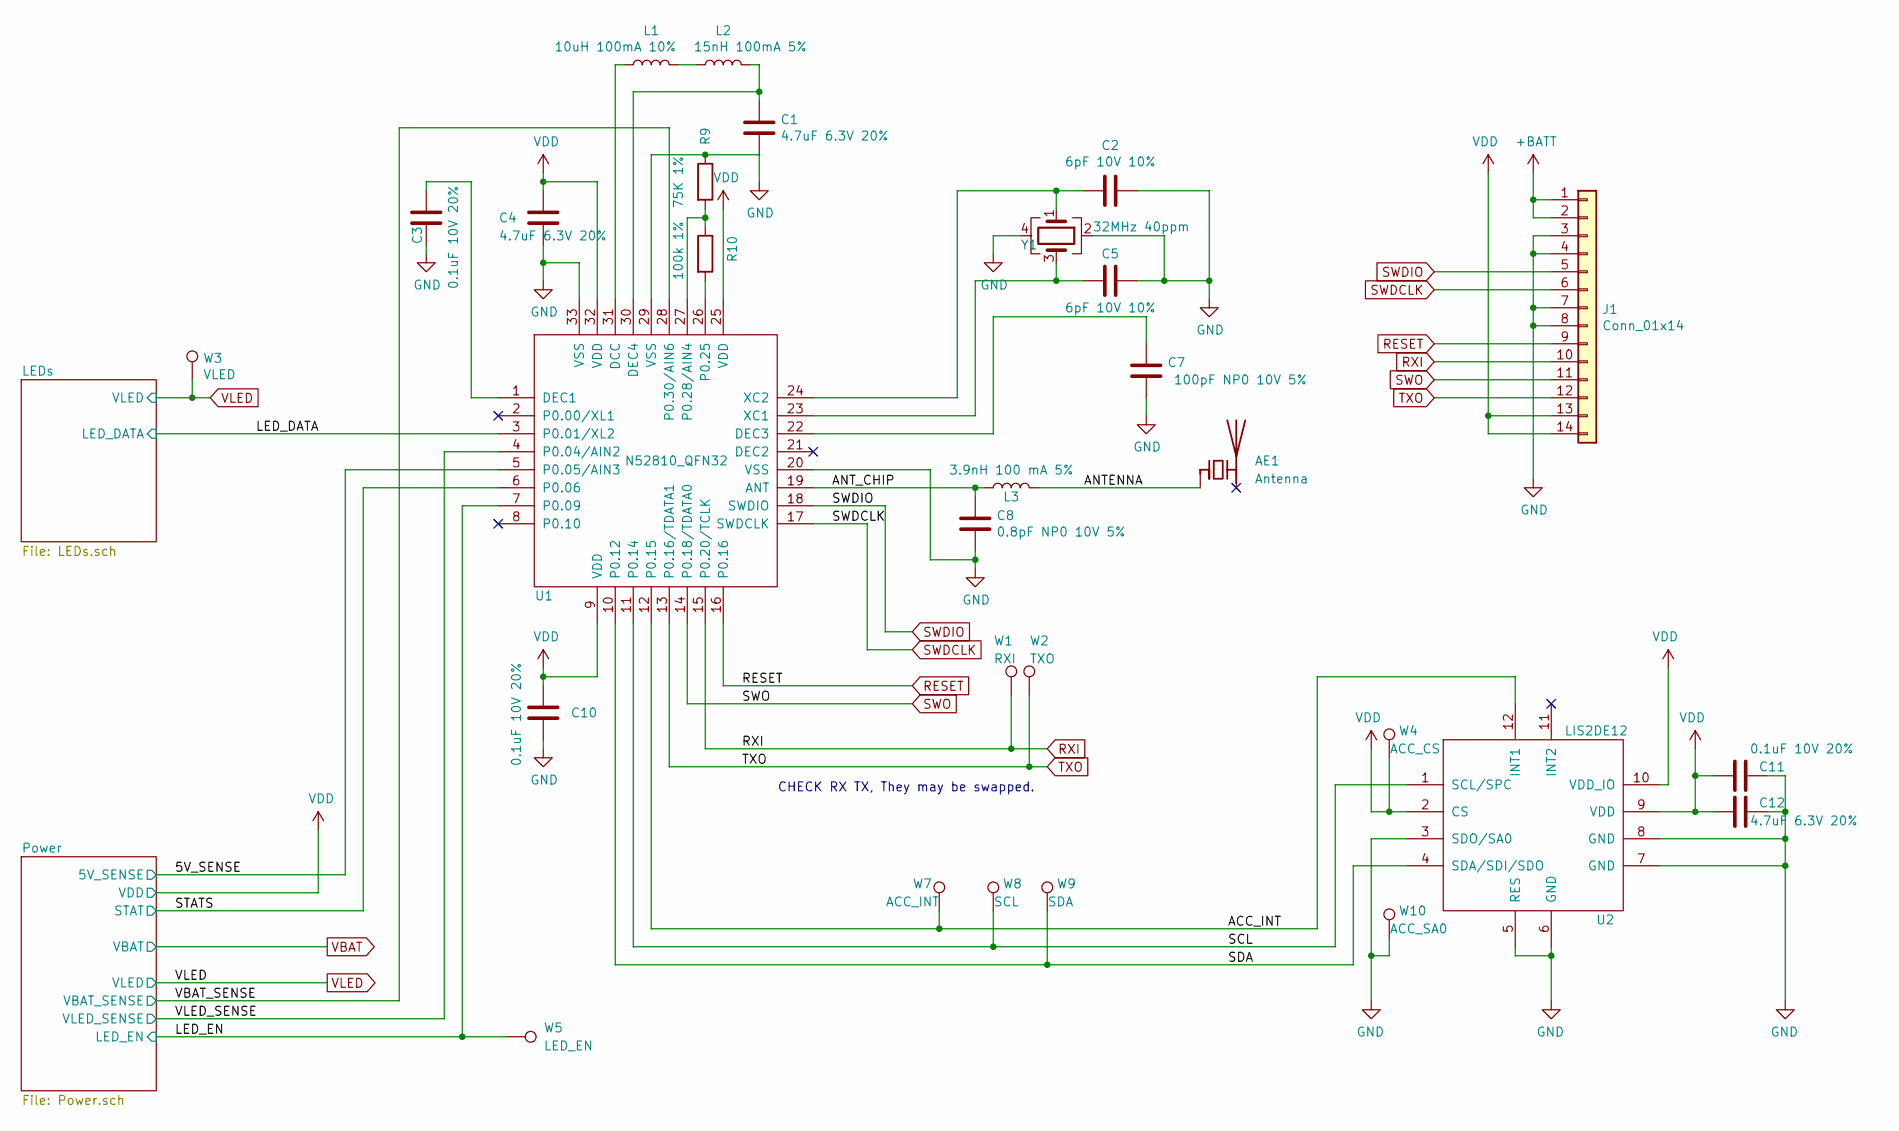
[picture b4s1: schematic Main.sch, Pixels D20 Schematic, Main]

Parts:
AE1: Antenna; CHIP_ANT; Manufacturer Part Number AMCA31-2R450G-S1F-T3
C1, C4, C12: 4.7uF 6.3V 20%; C_0603_1608Metric; Manufacturer Part Number CL10A475MQ8NNNC
C2, C5: 6pF 10V 10%; C_0402_1005Metric; Manufacturer Part Number GCM1555C1H6R0DA16D
C3, C10, C11: 0.1uF 10V 20%; C_0402_1005Metric; Manufacturer Part Number GRM155R61H104KE19D
C7: 100pF NP0 10V 5%; C_0402_1005Metric; Manufacturer Part Number C0402C101J5GAC7411
C8: 0.8pF NP0 10V 5%; C_0402_1005Metric; Manufacturer Part Number GJM1555C1HR80DB01J
J1: Conn_01x14; FPC_14
L1: 10uH 100mA 10%; L_0805_2012Metric; Manufacturer Part Number LBR2012T100K
L2: 15nH 100mA 5%; L_0402_1005Metric; Manufacturer Part Number HK100515NJ-T
L3: 3.9nH 100 mA 5%; L_0402_1005Metric; Manufacturer Part Number LQG15HN3N9S02D
R9: 75K 1%; R_0402_1005Metric; Manufacturer Part Number CRCW040275K0FKEDHP
R10: 100k 1%; R_0402_1005Metric; Manufacturer Part Number CRCW0402100KFKEDC
U1: N52810_QFN32; QFN-32-1EP_5x5mm_P0.5mm_EP3.1x3.1mm; Manufacturer Part Number NRF52810-QCAA-R
U2: LIS2DE12; LGA-12_2x2mm_P0.5mm; Manufacturer Part Number LIS2DE12TR
W1: RXI; TEST_PIN
W2: TXO; TEST_PIN
W3: VLED; TEST_PIN
W4: ACC_CS; TEST_PIN
W5: LED_EN; TEST_PIN
W7: ACC_INT; TEST_PIN
W8: SCL; TEST_PIN
W9: SDA; TEST_PIN
W10: ACC_SA0; TEST_PIN
Y1: 32MHz 40ppm; Crystal_SMD_2016-4Pin_2.0x1.6mm; Manufacturer Part Number XRCGB32M000F2P00R0

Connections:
/5V_SENSE: U1.5 (P0.05/AIN3); also elsewhere on the board
/ACC_INT: U1.12 (P0.15), U2.12 (INT1), W7.1
/ANTENNA: AE1.1 (FEED), L3.2
/ANT_CHIP: C8.1, L3.1, U1.19 (ANT)
/LED_DATA: U1.3 (P0.01/XL2); also elsewhere on the board
/LED_EN: U1.7 (P0.09), W5.1; also elsewhere on the board
/SCL: U1.11 (P0.14), U2.1 (SCL/SPC), W8.1
/SDA: U1.10 (P0.12), U2.4 (SDA/SDI/SDO), W9.1
/STATS: U1.6 (P0.06); also elsewhere on the board
/VBAT_SENSE: U1.28 (P0.30/AIN6); also elsewhere on the board
/VLED_SENSE: U1.4 (P0.04/AIN2); also elsewhere on the board
GND: C1.2, C2.1, C3.2, C4.2, C5.1, C7.2, C8.2, C10.2, C11.1, C12.1, J1.3, J1.4, J1.7, J1.8, R9.1, U1.20 (VSS), U1.29 (VSS), U1.33 (VSS), U2.3 (SDO/SA0), U2.5 (RES), U2.6 (GND), U2.7 (GND), U2.8 (GND), W10.1, Y1.2, Y1.4; also elsewhere on the board
unnamed: C1.1, L2.2, U1.30 (DEC4)
unnamed: C2.2, U1.24 (XC2), Y1.1
unnamed: C3.1, U1.1 (DEC1)
unnamed: C5.2, U1.23 (XC1), Y1.3
unnamed: C7.1, U1.22 (DEC3)
unnamed: L1.1, U1.31 (DCC)
unnamed: L1.2, L2.1
unnamed: R9.2, R10.1, U1.27 (P0.28/AIN4)
unnamed: R10.2, U1.26 (P0.25)
RESET: J1.9, U1.16 (P0.16)
RXI: J1.10, U1.15 (P0.20/TCLK), W1.1
SWDCLK: J1.6, U1.17 (SWDCLK)
SWDIO: J1.5, U1.18 (SWDIO)
SWO: J1.11, U1.14 (P0.18/TDATA0)
TXO: J1.12, U1.13 (P0.16/TDATA1), W2.1
VBAT: J1.1, J1.2; also elsewhere on the board
VDD: C4.1, C10.1, C11.2, C12.2, J1.13, J1.14, U1.9 (VDD), U1.25 (VDD), U1.32 (VDD), U2.2 (CS), U2.9 (VDD), U2.10 (VDD_IO), W4.1; also elsewhere on the board
VLED: W3.1; also elsewhere on the board

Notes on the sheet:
CHECK RX TX, They may be swapped.
